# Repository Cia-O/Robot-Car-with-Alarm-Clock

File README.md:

# Robot-Car-with-Alarm-Clock
This is a moving alarm clock  repository, that will features as much as we can schematics and code

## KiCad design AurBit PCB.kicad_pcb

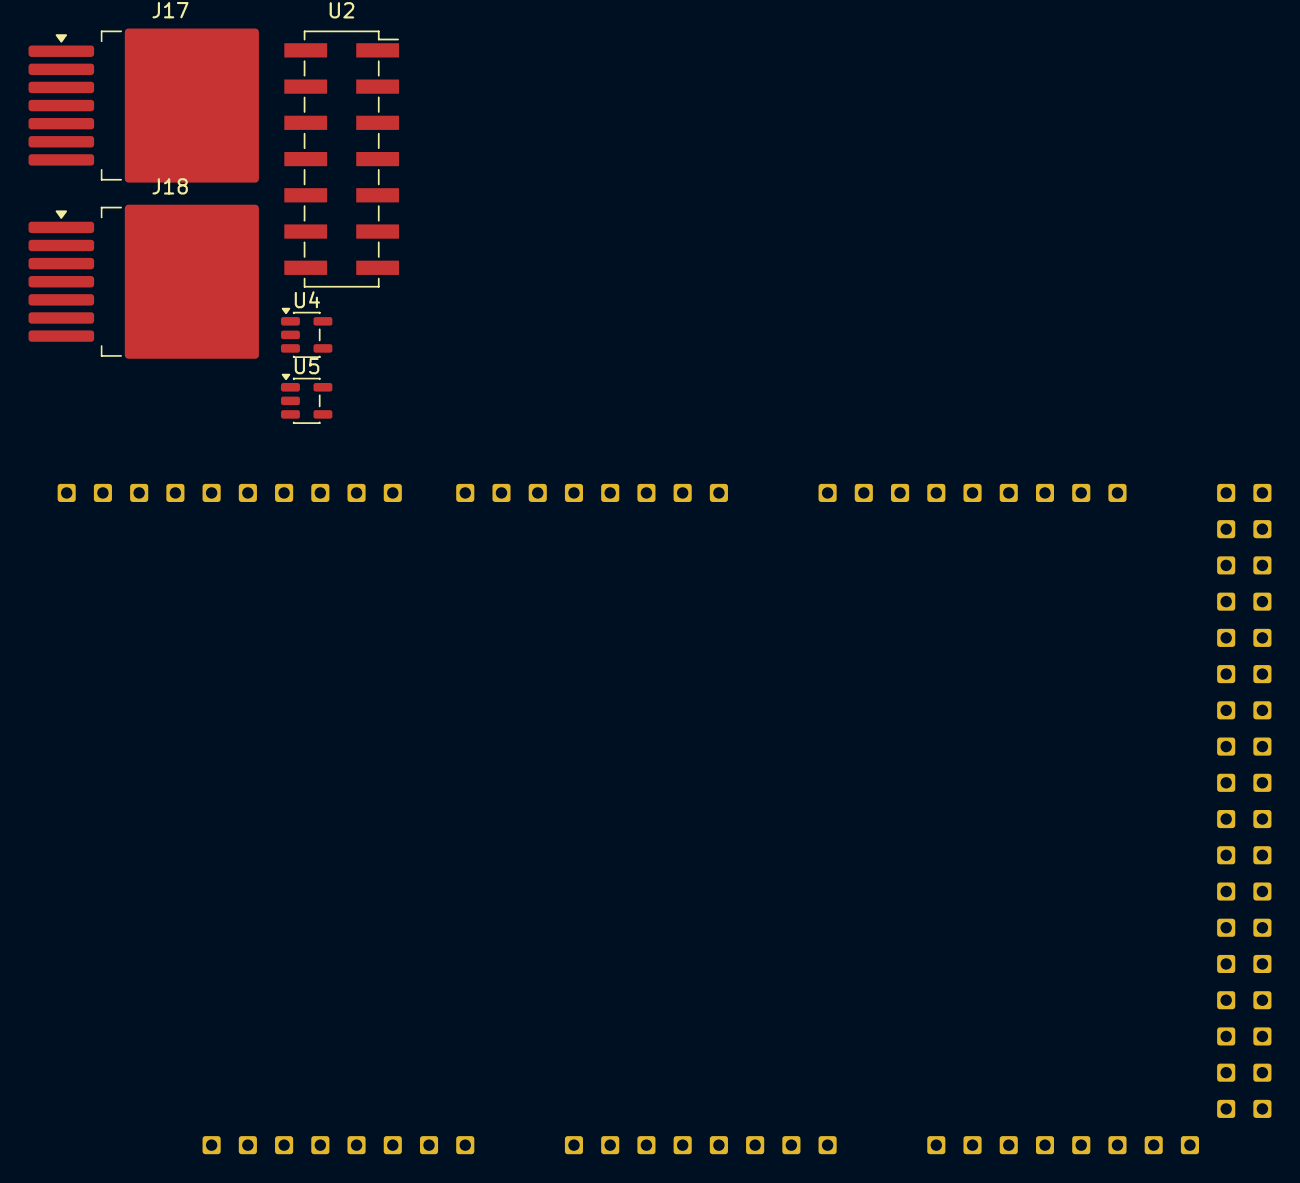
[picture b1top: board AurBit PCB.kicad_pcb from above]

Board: 2 copper layers, 6 parts (0 on the bottom side), 8 nets, no tracks yet.

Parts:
J17: RTC DS3231; TO-263-7_TabPin8
J18: Simplified ESP32; TO-263-7_TabPin8
U1: Arduino Mega 2560; AurBit_Arduino_Mega_2560_R3
U2: Adafruit DRV8833 Breakout; PinSocket_2x07_P2.54mm_Vertical_SMD
U4: LED DRIVER 1; TSOT-23-5
U5: LED DRIVER 2; TSOT-23-5

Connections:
+5V: J17.3 (VCC), J18.3 (GND), U1.66 (5V), U2.3 (SLP), U4.5 (VIN), U5.5 (VIN)
GND: J17.4 (GND), J18.4 (VBUS(5V)), U1.65 (GND), U2.1 (GND), U4.2 (GND), U5.2 (GND)
unnamed: J17.1 (SCL), U1.25 (SCL)
unnamed: J17.2 (SDA), U1.24 (SDA)
unnamed: U1.31 (25), U2.6 (AIN2)
unnamed: U1.33 (27), U2.8 (BIN2)
unnamed: U1.12 (pwm5), U2.5 (AIN1)
unnamed: U1.10 (pwm7), U2.7 (BIN1)
